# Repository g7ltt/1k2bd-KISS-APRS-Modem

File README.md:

# 1k2bd-KISS-APRS-Modem
1200bd AX.25 KISS/APRS Modem

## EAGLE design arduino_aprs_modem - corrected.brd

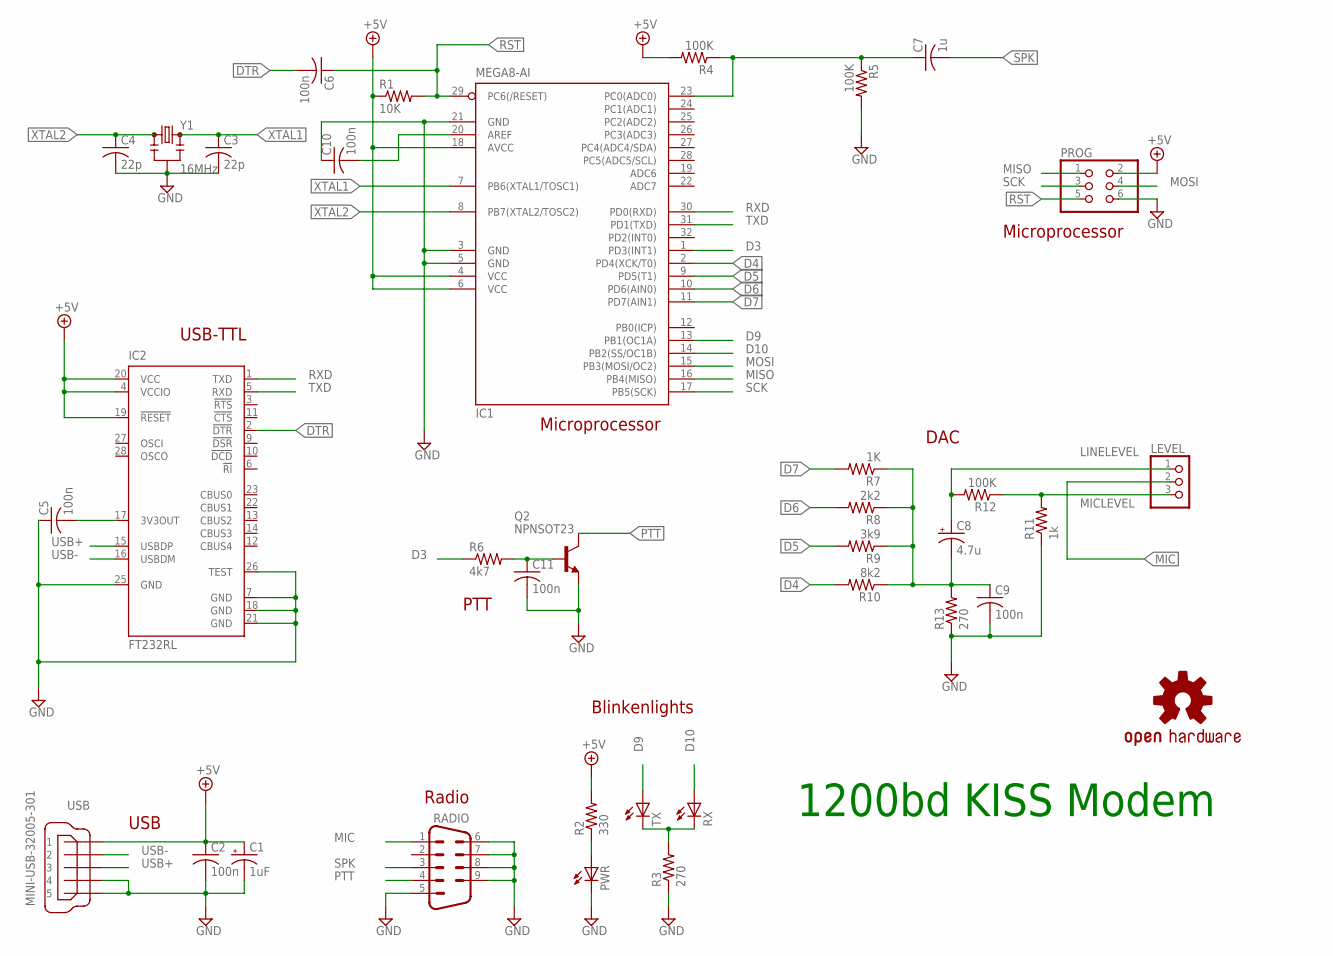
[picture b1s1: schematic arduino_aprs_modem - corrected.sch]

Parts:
C1: 1uF; E2-5
C2, C5, C6, C9, C10, C11: 100n; C0805
C3, C4: 22p; C0805
C7: 1u; C0805
C8: 4.7u; E2-5
IC1: MEGA8-AI; TQFP32-08
IC2: FT232RL; SSOP28
LEVEL: PINHD-1X3; 1X03
PROG: PINHD-2X3; 2X03
PWR: LEDCHIPLED_0805; CHIPLED_0805
Q2: NPNSOT23; SOT23
R1: 10K; M0805
R2: 330; M0805
R3, R13: 270; M0805
R4, R5, R12: 100K; M0805
R6: 4k7; M0805
R7: 1K; M0805
R8: 2k2; M0805
R9: 3k9; M0805
R10: 8k2; M0805
R11: 1k; M0805
RADIO: M09H
RX: LEDCHIPLED_0805; CHIPLED_0805
TX: LEDCHIPLED_0805; CHIPLED_0805
U$1: OSHW-LOGOM; OSHW-LOGO-M
USB: MINI-USB-32005-301; 32005-301
Y1: 16MHz; RESONATOR-PTH

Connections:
+5V: C1.+, C2.1, IC1.4 (VCC), IC1.6 (VCC), IC1.18 (AVCC), IC2.4 (VCCIO), IC2.19 (!RESET), IC2.20 (VCC), PROG.2, R1.1, R2.2, R4.2, USB.1
D3: IC1.1 (PD3(INT1)), R6.1
D4: IC1.2 (PD4(XCK/T0)), R10.2
D5: IC1.9 (PD5(T1)), R9.2
D6: IC1.10 (PD6(AIN0)), R8.2
D7: IC1.11 (PD7(AIN1)), R7.2
D9: IC1.13 (PB1(OC1A)), TX.A
D10: IC1.14 (PB2(SS/OC1B)), RX.A
DTR: C6.2, IC2.2 (!DTR)
GND: C1.-, C2.2, C3.2, C4.2, C5.1, C9.2, C10.1, C11.2, IC1.3 (GND), IC1.5 (GND), IC1.21 (GND), IC2.7 (GND), IC2.18 (GND), IC2.21 (GND), IC2.25 (GND), IC2.26 (TEST), PROG.6, PWR.C, Q2.2 (E), R3.1, R5.2, R11.1, R13.1, RADIO.5, RADIO.6, RADIO.7, RADIO.8, RADIO.9, USB.4, USB.5, Y1.2
LINELEVEL: C8.+, LEVEL.1, R12.2
MIC: LEVEL.2, RADIO.1
MICLEVEL: LEVEL.3, R11.2, R12.1
MISO: IC1.16 (PB4(MISO)), PROG.1
MOSI: IC1.15 (PB3(MOSI/OC2)), PROG.4
unnamed: C10.2, IC1.20 (AREF)
unnamed: PWR.A, R2.1
unnamed: R3.2, RX.C, TX.C
unnamed: C7.1, IC1.23 (PC0(ADC0)), R4.1, R5.1
unnamed: C11.1, Q2.1 (B), R6.2
unnamed: C5.2, IC2.17 (3V3OUT)
unnamed: C8.-, C9.1, R7.1, R8.1, R9.1, R10.1, R13.2
PTT: Q2.3 (C), RADIO.4
RST: C6.1, IC1.29 (PC6(/RESET)), PROG.5, R1.2
RXD: IC1.30 (PD0(RXD)), IC2.1 (TXD)
SCK: IC1.17 (PB5(SCK)), PROG.3
SPK: C7.2, RADIO.3
TXD: IC1.31 (PD1(TXD)), IC2.5 (RXD)
USB+: IC2.15 (USBDP), USB.3
USB-: IC2.16 (USBDM), USB.2
XTAL1: C3.1, IC1.7 (PB6(XTAL1/TOSC1)), Y1.3
XTAL2: C4.1, IC1.8 (PB7(XTAL2/TOSC2)), Y1.1

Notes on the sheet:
1200bd KISS Modem
Microprocessor
USB-TTL
DAC
PTT
Radio
Blinkenlights
USB

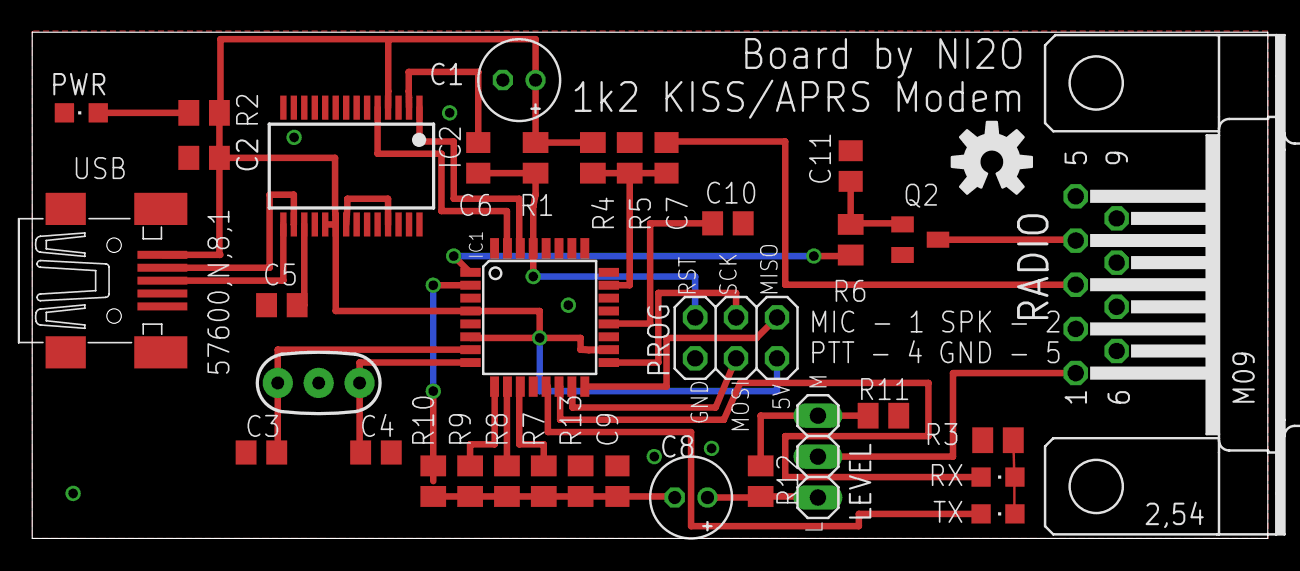
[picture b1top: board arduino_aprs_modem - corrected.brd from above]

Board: 2 copper layers, 76.7 x 31.4 mm, 36 parts (0 on the bottom side), 32 nets.

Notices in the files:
parts and their libraries:
SparkFun: Licensing: CC v3.0 Share-Alike You are welcome to use this library for commercial purposes.
SparkFun-FreqCtrl: Licensing: Creative Commons ShareAlike 4.0 International - https://creativecommons.org/licenses/by-sa/4.0
